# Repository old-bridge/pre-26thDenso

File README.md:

# pre-26thDenso
for prototyping 26denso

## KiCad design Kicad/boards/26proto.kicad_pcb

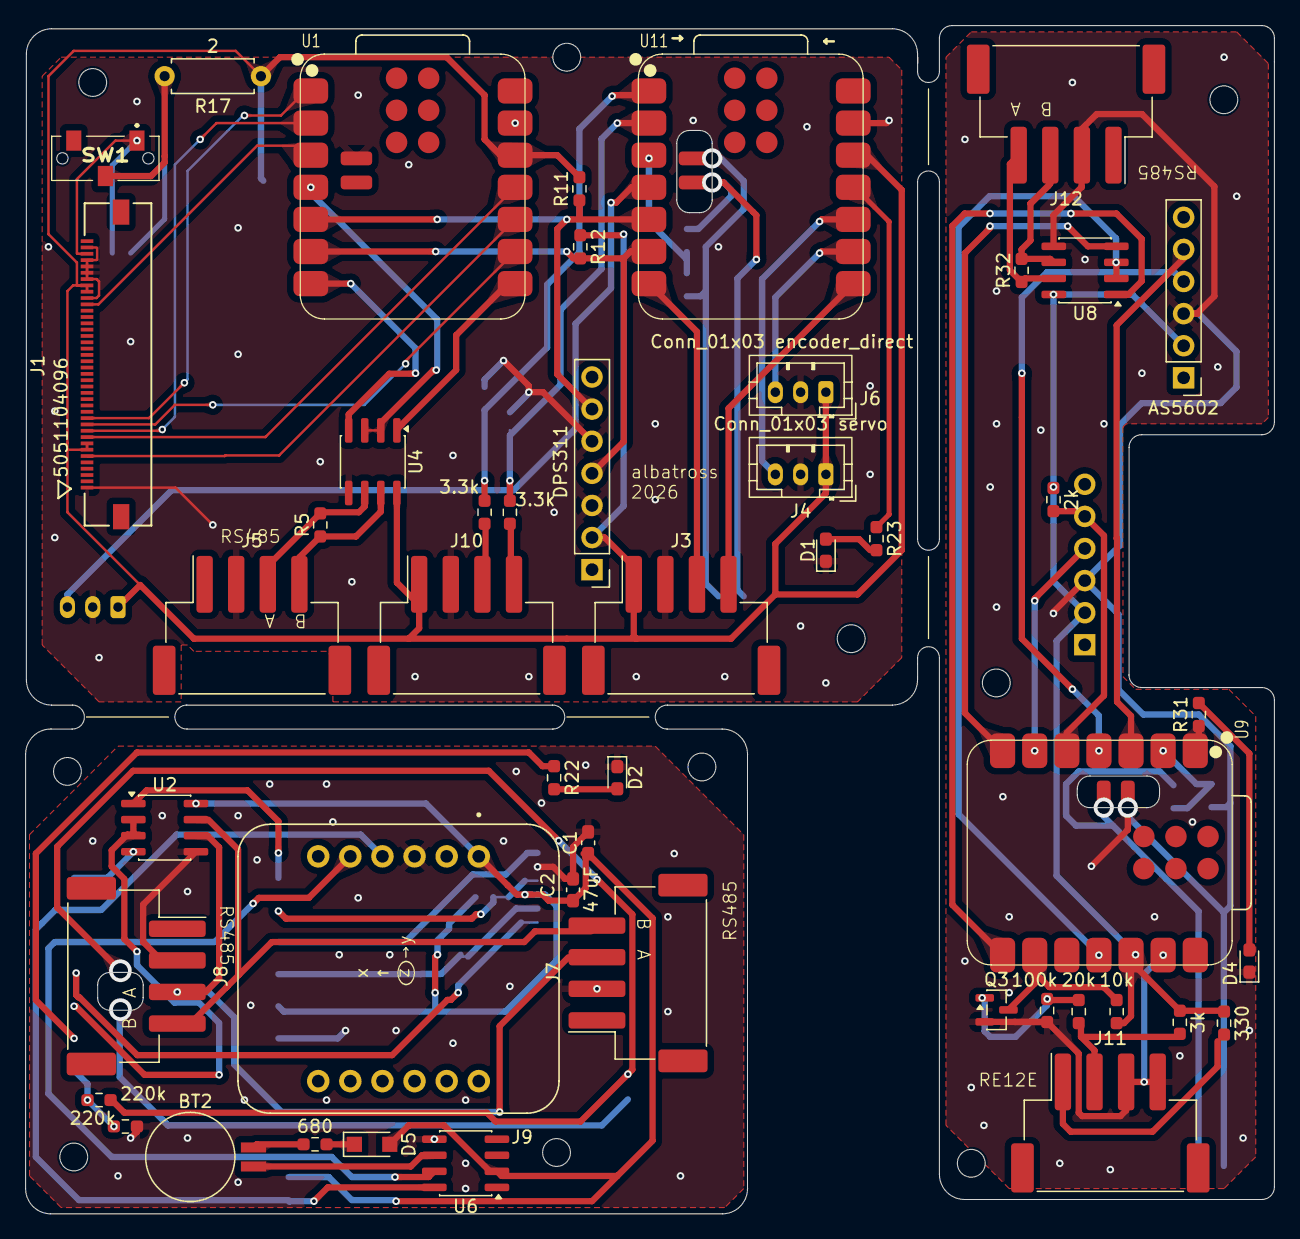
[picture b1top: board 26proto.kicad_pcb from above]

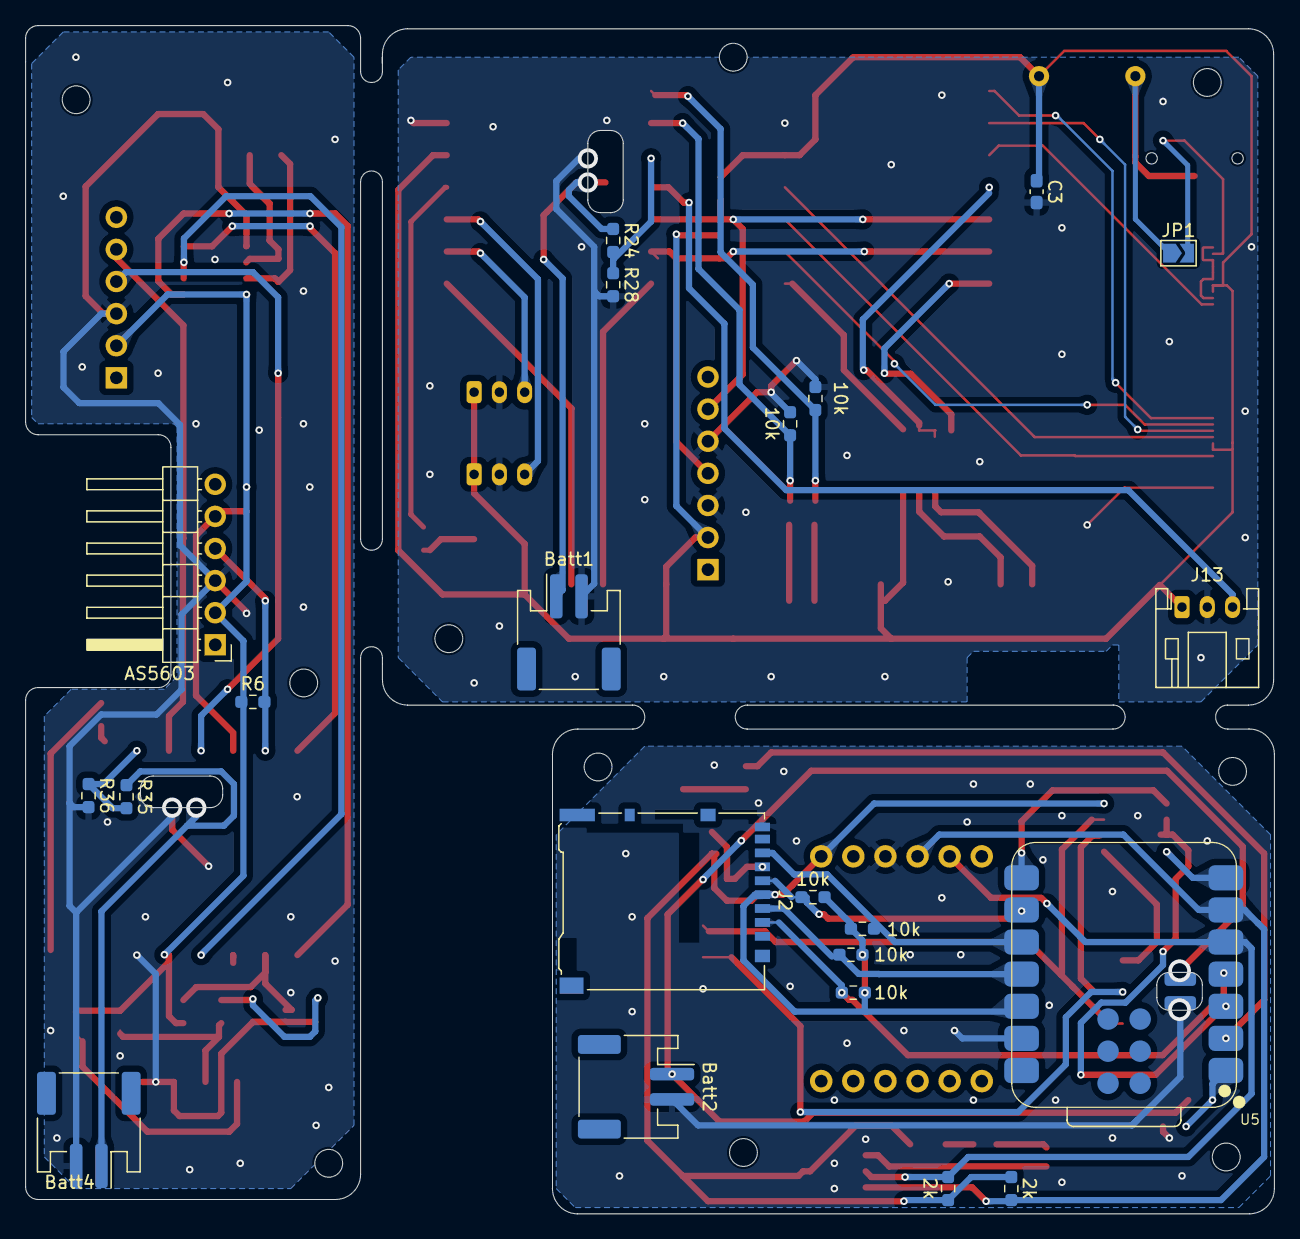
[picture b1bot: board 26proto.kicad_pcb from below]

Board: 2 copper layers, 98.8 x 94.0 mm, 70 parts (22 on the bottom side), 69 nets.

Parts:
AS5602: AoS; PinHeader_1x06_P2.54mm_Vertical
AS5603: AoA; PinHeader_1x06_P2.54mm_Horizontal
BT2: MS621; BatteryHolder_Seiko_MS621F
Batt1, Batt2, Batt4: Conn_01x02; JST_PH_S2B-PH-SM4-TB_1x02-1MP_P2.00mm_Horizontal
C1: 0.1uF; C_0603_1608Metric_Pad1.08x0.95mm_HandSolder
C2, C3: 47uF; C_0603_1608Metric_Pad1.08x0.95mm_HandSolder
D1, D2, D4: LED; LED_0603_1608Metric_Pad1.05x0.95mm_HandSolder
D5: D; Nexperia_CFP3_SOD-123W
DPS311: Adafruit DPS310; PinHeader_1x07_P2.54mm_Vertical
J1: 5051104096; CON_5051104096_MOL
J2: Micro_SD_Card; microSD_HC_Hirose_DM3AT-SF-PEJM5
J3: URM37; JST_XH_S4B-XH-SM4-TB_1x04-1MP_P2.50mm_Horizontal
J4: Conn_01x03 servo; JST_PH_B3B-PH-K_1x03_P2.00mm_Vertical
J5: RS485_TFT; JST_XH_S4B-XH-SM4-TB_1x04-1MP_P2.50mm_Horizontal
J6: Conn_01x03 encoder_direct; JST_PH_B3B-PH-K_1x03_P2.00mm_Vertical
J7: RS485_logger_2; JST_XH_S4B-XH-SM4-TB_1x04-1MP_P2.50mm_Horizontal
J8: RS485_logger; JST_XH_S4B-XH-SM4-TB_1x04-1MP_P2.50mm_Horizontal
J9: BNO085; MODULE_4754_without_holes
J10: Conn_01x04; JST_XH_S4B-XH-SM4-TB_1x04-1MP_P2.50mm_Horizontal
J11: RE12A; JST_XH_S4B-XH-SM4-TB_1x04-1MP_P2.50mm_Horizontal
J12: RS485_airdata; JST_XH_S4B-XH-SM4-TB_1x04-1MP_P2.50mm_Horizontal
J13: Conn_01x03 speaker; JST_PH_S3B-PH-K_1x03_P2.00mm_Horizontal
JP1: SolderJumper_2_Open; SolderJumper-2_P1.3mm_Open_TrianglePad1.0x1.5mm
Q3: NPN; SOT-23
R1, R2, R3, R9, R13, R18, R30: 10k; R_0603_1608Metric_Pad0.98x0.95mm_HandSolder
R4: 680; R_0603_1608Metric_Pad0.98x0.95mm_HandSolder
R5, R32: 120; R_0603_1608Metric_Pad0.98x0.95mm_HandSolder
R6, R7, R8, R11, R12, R14: 2k; R_0603_1608Metric_Pad0.98x0.95mm_HandSolder
R10, R20: 3.3k; R_0603_1608Metric_Pad0.98x0.95mm_HandSolder
R17: 2; R_Axial_DIN0207_L6.3mm_D2.5mm_P7.62mm_Horizontal
R22, R23, R31: 100; R_0603_1608Metric_Pad0.98x0.95mm_HandSolder
R24, R28, R33, R34, R35, R36: 220k; R_0603_1608Metric_Pad0.98x0.95mm_HandSolder
R25: 20k; R_0603_1608Metric_Pad0.98x0.95mm_HandSolder
R26: 330; R_0603_1608Metric_Pad0.98x0.95mm_HandSolder
R27: 3k; R_0603_1608Metric_Pad0.98x0.95mm_HandSolder
R29: 100k; R_0603_1608Metric_Pad0.98x0.95mm_HandSolder
SW1: SW_DIP_x01; CLSB12A02T
U1: MOUDLE-SEEEDUINO-XIAO-ESP32C3_TFT; XIAO-ESP32C3-SMD
U2, U4, U8: MAX3485; SOIC-8_3.9x4.9mm_P1.27mm
U5: MOUDLE-SEEEDUINO-XIAO-ESP32C3_logger; XIAO-ESP32C3-SMD
U6: DS3231MZ; SOIC-8_3.9x4.9mm_P1.27mm
U9: MOUDLE-SEEEDUINO-XIAO-ESP32C3_airdata; XIAO-ESP32C3-SMD
U11: MOUDLE-SEEEDUINO-XIAO-ESP32C3_pot; XIAO-ESP32C3-SMD

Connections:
+3.3V-1: AS5602.2 (3V3), AS5603.2 (3V3), R6.1, R14.1, R26.1, R27.1, R30.1, U8.8 (VCC), U9.12 (3V3)
+3.3V-2: C1.1, C2.1, D5.2 (A), J2.4 (VDD), J9.JP1_1 (VIN), R1.2, R2.2, R3.2, R7.1, R8.1, R13.2, U2.8 (VCC), U5.12 (3V3), U6.2 (VCC)
+3.3V-3: C3.1, DPS311.2 (3Vo), J1.7, J1.8, J1.32, J1.33, J3.1, J4.1, J6.1, J10.1, J13.1, R11.2, R12.1, R17.1, U1.12 (3V3), U4.8 (VCC), U11.12 (3V3)
+BATT-1: Batt4.1, R35.1, U9.15 (BAT)
+BATT-2: Batt2.1, R33.1, U5.15 (BAT)
+BATT-3: Batt1.1, R24.1, U11.15 (BAT)
/1. airdata/DE/RE: U8.2 (~RE), U8.3 (DE), U9.11 (GPIO10_D10_MOSI)
/1. airdata/RS485_A: J12.3, R32.2, U8.6 (A)
/1. airdata/RS485_B: J12.4, R32.1, U8.7 (B)
/1. airdata/SCL: AS5603.4 (SCL), R6.2, U9.6 (GPIO7_D5_SCL)
/1. airdata/SCL_soft: AS5602.4 (SCL), U9.4 (GPIO5_A3_D3)
/1. airdata/SDA: AS5603.5 (SDA), R14.2, U9.5 (GPIO6_D4_SDA)
/1. airdata/SDA_soft: AS5602.5 (SDA), U9.3 (GPIO4_A2_D2)
/1. airdata/V_check-1: R35.2, R36.1, U9.2 (GPIO3_A1_D1)
/1. airdata/encoder_out: Q3.3 (C), R30.2, U9.9 (GPIO8_D8_SCK)
/1. airdata/encoder_raw: Q3.1 (B), R25.2, R29.2
/2.logger/CS: J2.2 (DAT3/CD), R2.1, U5.4 (GPIO5_A3_D3)
/2.logger/DE/RE: U2.2 (~RE), U2.3 (DE), U5.3 (GPIO4_A2_D2)
/2.logger/MISO: J2.7 (DAT0), R3.1, U5.10 (GPIO9_D9_MISO)
/2.logger/MOSI: J2.3 (CMD), R1.1, U5.11 (GPIO10_D10_MOSI)
/2.logger/SCL: J9.JP1_4 (SCL), R8.2, U5.6 (GPIO7_D5_SCL), U6.8 (SCL)
/2.logger/SCLK: J2.5 (CLK), R13.1, U5.9 (GPIO8_D8_SCK)
/2.logger/SDA: J9.JP1_5 (SDA), R7.2, U5.5 (GPIO6_D4_SDA), U6.7 (SDA)
/2.logger/V_check-2: R33.2, R34.1, U5.1 (GPIO2_A0_D0)
/3. TFT/CS: J1.10, U1.2 (GPIO3_A1_D1)
/3. TFT/DCX-SCLK: J1.11, U1.9 (GPIO8_D8_SCK)
/3. TFT/DE/RE: U1.4 (GPIO5_A3_D3), U4.2 (~RE), U4.3 (DE)
/3. TFT/Pot_elv: R9.1, R10.1, U11.1 (GPIO2_A0_D0)
/3. TFT/Pot_rud: R18.1, R20.1, U11.2 (GPIO3_A1_D1)
/3. TFT/RES: J1.30, U1.3 (GPIO4_A2_D2)
/3. TFT/RS485_A: J5.3, R5.2, U4.6 (A)
/3. TFT/RS485_B: J5.4, R5.1, U4.7 (B)
/3. TFT/RX: J3.4, U11.8 (GPIO20_D7_RX)
/3. TFT/RX_encoder: J6.3, U11.9 (GPIO8_D8_SCK)
/3. TFT/SCL: DPS311.4 (SCK), R12.2, U1.6 (GPIO7_D5_SCL), U11.6 (GPIO7_D5_SCL)
/3. TFT/SDA: DPS311.6 (SDI), R11.1, U1.5 (GPIO6_D4_SDA), U11.5 (GPIO6_D4_SDA)
/3. TFT/SDA-MOSI: J1.9, U1.11 (GPIO10_D10_MOSI)
/3. TFT/SDO-MISO: J1.6, U1.10 (GPIO9_D9_MISO)
/3. TFT/Speaker: J13.3, U11.4 (GPIO5_A3_D3)
/3. TFT/TX: J3.3, U11.7 (GPIO21_D6_TX)
/3. TFT/V_check-3: R24.2, R28.1, U11.3 (GPIO4_A2_D2)
/3. TFT/WRX-D/C: J1.12, U1.1 (GPIO2_A0_D0)
/3. TFT/servo: J4.3, U11.10 (GPIO9_D9_MISO)
GND-1: AS5602.3 (GND), AS5603.3 (GND), Batt4.2, D4.1 (K), J11.3, J11.4, J12.2, Q3.2 (E), R29.1, R36.2, U8.5 (GND), U9.13 (GND), U9.16 (GND)
GND-2: Batt2.2, C1.2, C2.2, D2.1 (K), J2.6 (VSS), J2.9 (SHIELD), J7.2, J8.2, J9.JP1_3 (GND), R34.2, U2.5 (GND), U5.13 (GND), U5.16 (GND), U6.5 (GND)
GND-3: Batt1.2, C3.2, D1.1 (K), DPS311.3 (GND), DPS311.5 (SDO), J1.1, J1.31, J1.34, J1.35, J1.36, J1.37, J1.39, J3.2, J4.2, J5.2, J6.2, J10.2, J13.2, R9.2, R18.2, R28.2, U1.13 (GND), U1.16 (GND), U4.5 (GND), U11.13 (GND), U11.16 (GND)
unnamed: BT2.1 (+), R4.1
unnamed: BT2.2 (-), U6.6 (VBAT)
unnamed: D1.2 (A), R23.2
unnamed: D2.2 (A), R22.2
unnamed: D4.2 (A), R31.2
unnamed: D5.1 (K), R4.2
unnamed: J10.3, R10.2
unnamed: J10.4, R20.2
unnamed: J11.1, R26.2
unnamed: J11.2, R25.1, R27.2
unnamed: JP1.1 (A), R17.2, SW1.2
unnamed: J1.38, JP1.2 (B), SW1.1
unnamed: U1.8 (GPIO20_D7_RX), U4.1 (RO)
unnamed: U1.7 (GPIO21_D6_TX), U4.4 (DI)
unnamed: U2.4 (DI), U5.7 (GPIO21_D6_TX)
unnamed: U2.1 (RO), U5.8 (GPIO20_D7_RX)
unnamed: R22.1, U5.2 (GPIO3_A1_D1)
unnamed: U8.4 (DI), U9.7 (GPIO21_D6_TX)
unnamed: U8.1 (RO), U9.8 (GPIO20_D7_RX)
unnamed: R31.1, U9.1 (GPIO2_A0_D0)
unnamed: R23.1, U11.11 (GPIO10_D10_MOSI)
RS485_A: J7.3, J8.3, U2.6 (A)
RS485_B: J7.4, J8.4, U2.7 (B)

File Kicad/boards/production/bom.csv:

Designator,Footprint,Quantity,Value,LCSC Part #
AS5602,PinHeader_1x06_P2.54mm_Vertical,1,AoS,
AS5603,PinHeader_1x06_P2.54mm_Horizontal,1,AoA,
"BATT1, BATT2, BATT4",JST_PH_S2B-PH-SM4-TB_1x02-1MP_P2.00mm_Horizontal,3,Conn_01x02,
BT2,BatteryHolder_Seiko_MS621F,1,MS621,
C1,0603,1,0.1uF,
"C2, C3",0603,2,47uF,
"D1, D2, D4",0603,3,LED,
D5,Nexperia_CFP3_SOD-123W,1,D,
DPS311,PinHeader_1x07_P2.54mm_Vertical,1,Adafruit DPS310,
J1,CON_5051104096_MOL,1,5051104096,
J10,JST_XH_S4B-XH-SM4-TB_1x04-1MP_P2.50mm_Horizontal,1,Conn_01x04,
J11,JST_XH_S4B-XH-SM4-TB_1x04-1MP_P2.50mm_Horizontal,1,RE12A,
J12,JST_XH_S4B-XH-SM4-TB_1x04-1MP_P2.50mm_Horizontal,1,RS485_airdata,
J13,JST_PH_S3B-PH-K_1x03_P2.00mm_Horizontal,1,Conn_01x03 speaker,
J2,microSD_HC_Hirose_DM3AT-SF-PEJM5,1,Micro_SD_Card,
J3,JST_XH_S4B-XH-SM4-TB_1x04-1MP_P2.50mm_Horizontal,1,URM37,
J4,JST_PH_B3B-PH-K_1x03_P2.00mm_Vertical,1,Conn_01x03 servo,
J5,JST_XH_S4B-XH-SM4-TB_1x04-1MP_P2.50mm_Horizontal,1,RS485_TFT,
J6,JST_PH_B3B-PH-K_1x03_P2.00mm_Vertical,1,Conn_01x03 encoder_direct,
J7,JST_XH_S4B-XH-SM4-TB_1x04-1MP_P2.50mm_Horizontal,1,RS485_logger_2,
J8,JST_XH_S4B-XH-SM4-TB_1x04-1MP_P2.50mm_Horizontal,1,RS485_logger,
J9,MODULE_4754_without_holes,1,BNO085,
Q3,SOT-23,1,NPN,
"R1, R13, R18, R2, R3, R30, R9",0603,7,10k,
"R10, R20",0603,2,3.3k,
"R11, R12, R14, R6, R7, R8",0603,6,2k,
R17,R_Axial_DIN0207_L6.3mm_D2.5mm_P7.62mm_Horizontal,1,2,
"R22, R23, R31",0603,3,100,
"R24, R28, R33, R34, R35, R36",0603,6,220k,
R25,0603,1,20k,
R26,0603,1,330,
R27,0603,1,3k,
R29,0603,1,100k,
"R32, R5",0603,2,120,
R4,0603,1,680,
SW1,CLSB12A02T,1,SW_DIP_x01,
U1,XIAO-ESP32C3-SMD,1,MOUDLE-SEEEDUINO-XIAO-ESP32C3_TFT,
U11,XIAO-ESP32C3-SMD,1,MOUDLE-SEEEDUINO-XIAO-ESP32C3_pot,
"U2, U4, U8",SOIC-8_3.9x4.9mm_P1.27mm,3,MAX3485,
U5,XIAO-ESP32C3-SMD,1,MOUDLE-SEEEDUINO-XIAO-ESP32C3_logger,
U6,SOIC-8_3.9x4.9mm_P1.27mm,1,DS3231MZ,
U9,XIAO-ESP32C3-SMD,1,MOUDLE-SEEEDUINO-XIAO-ESP32C3_airdata,

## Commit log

2025-11-03 created kicad files
2025-11-03 changed names
2025-11-06 connector
2025-11-07 edited sch
2025-11-07 edited schimatic
2025-11-17 upgraded schema
2025-11-17 updated pcb
2025-11-17 update sch
2025-11-18 updated sch
2025-11-19 edited pcb
2025-11-20 edited sch and pcb
2025-11-20 Add battery connector and update net assignments
    Added Batt1 JST PH connector footprint and R4 resistor for RS485 lines. Updated net assignments for U11 pins, replaced encoder_anode with +3.3V and pot_Vin where appropriate, and made related schemat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
2025-11-21 updated TFT and sensors board
2025-11-22 added I2C wires
2025-11-22 updated logger and IMU board
2025-11-23 updated IMU board
2025-12-06 edited airdata board
2025-12-10 Create airdata
2025-12-15 conflict?
2025-12-15 added RTC
2025-12-15 added mosfet
2025-12-22 add resister values
2025-12-22 add voltage divide resistor
2025-12-27 added LED
2025-12-28 added jumper
2026-01-08 一旦完成
2026-01-10 edited
2026-01-19 2026/01
    2026/01
2026-02-06 0206
2026-02-06 0206_2
2026-02-08 電源1つに
2026-02-14 added code files
2026-02-15 edited boards
2026-02-24 基板発注
